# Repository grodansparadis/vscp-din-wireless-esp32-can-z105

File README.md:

# vscp-din-wireless-esp32-z105
ESP32 based CAN4VSCP FD controller in a single module DIN package with BT and wifi interface.

**Note!** This is still a prototype. ....

The bottom board is here: https://github.com/grodansparadis/vscp-din-m1-base-board-z105

## PCB's

---

Part of the [VSCP Project](https://www.vscp.org).

Copyright 2021-2026 © Åke Hedman, (Grodans Paradis AB)[https://www.grodansparadis.com]

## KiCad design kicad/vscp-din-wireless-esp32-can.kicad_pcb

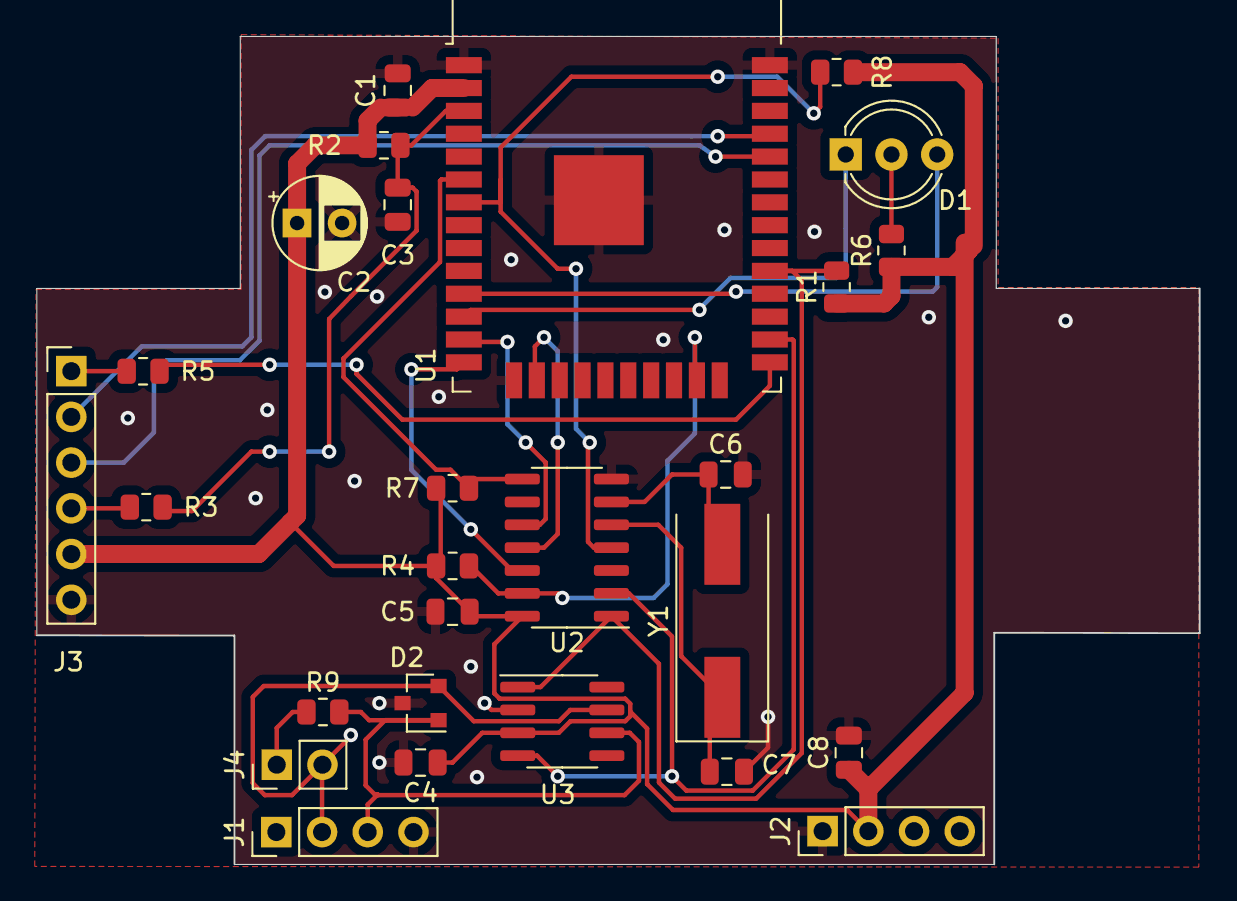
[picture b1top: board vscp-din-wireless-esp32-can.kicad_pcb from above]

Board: 2 copper layers, 64.6 x 46.0 mm, 27 parts (0 on the bottom side), 24 nets.

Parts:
C1, C3, C4, C5, C8: 100nF; C_0805_2012Metric
C2: 10uF; CP_Radial_D5.0mm_P2.50mm
C6, C7: 22pF; C_0805_2012Metric
D1: LED_Dual_CAC; LED_D5.0mm-3
D2: NUP2105L; SOT-23
J1: Conn_Left_I2C; PinHeader_1x04_P2.54mm_Vertical
J2: Conn_Right_Power; PinHeader_1x04_P2.54mm_Vertical
J3: Conn_01x06; PinHeader_1x06_P2.54mm_Vertical
J4: Conn_01x02; PinHeader_1x02_P2.54mm_Vertical
R1, R2, R4, R7, R8: 10K; R_0805_2012Metric
R3, R5, R6: 470; R_0805_2012Metric
R9: 120R; R_0805_2012Metric
U1: ESP32-WROOM-32D; ESP32-WROOM-32
U2: MCP2517FD-xSL; SOIC-14_3.9x8.7mm_P1.27mm
U3: SN65HVD232; SOIC-8_3.9x4.9mm_P1.27mm
Y1: 4MHz; Crystal_SMD_HC49-SD

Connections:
/CS: R4.2, U1.23 (IO15), U2.13 (nCS)
/FLASH: J3.1, R5.2
/MISO: U1.14 (IO12), U2.12 (SDO)
/MOSI: U1.16 (IO13), U2.11 (SDI)
/RESET: J3.4, R3.1
/RXD: J3.3, U1.34 (RXD0/IO3)
/SCK: U1.13 (IO14), U2.10 (SCK)
/TXD: J3.2, U1.35 (TXD0/IO1)
/irq0: R8.1, U1.7 (IO35), U2.4 (~INT)
/irq1: R7.1, U1.6 (IO34), U2.8 (~INT1/GPIO1)
/leda: D1.3 (K2), U1.11 (IO26)
/ledb: D1.1 (K1), U1.12 (IO27)
/reset: C3.1, R2.2, R3.2, U1.3 (EN)
/rxcan: U1.26 (IO4), U2.2 (RXCAN), U3.4 (R)
/txcan: R1.2, U1.29 (IO5), U2.1 (TXCAN), U3.1 (D)
GND: C1.2, C2.2, C3.2, C4.2, C5.2, C6.2, C7.2, C8.2, D2.3 (A), J1.4, J2.1, J3.6, U1.1 (GND), U1.15 (GND), U1.38 (GND), U1.39 (GND), U2.7 (VSS), U3.2 (GND)
unnamed: D1.2 (A), R6.2
unnamed: D2.2 (K), J1.2, J4.2, U3.7 (CANH)
unnamed: D2.1 (K), J1.3, R9.2, U3.6 (CANL)
unnamed: J4.1, R9.1
unnamed: R5.1, U1.25 (IO0)
unnamed: C6.1, U2.6 (OSC1), Y1.2
unnamed: C7.1, U2.5 (OSC2), Y1.1
VCC: C1.1, C2.1, C4.1, C5.1, C8.1, J2.2, J3.5, R1.1, R2.1, R4.1, R6.1, R7.2, R8.2, U1.2 (VDD), U2.14 (VDD), U3.3 (VCC)

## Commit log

2021-05-24 Init import
2021-05-25 First version gerbers
2021-05-25 Added gerbers
2021-05-25 Added notes
2021-08-09 shrinked to fit encapsulationy
    Please enter the commit message for your changes. Lines starting
2021-08-09 Test
2022-02-03 Updatwd copyright
2022-06-15 Fixed some design errors
2022-06-16 Added CAN interace link
2022-06-17 Added BT/serial config info
2022-09-02 Added new libs
2022-09-02 Removed unused images
2022-09-02 Prepared repository name change
2025-06-05 Updated copyright year
2025-09-17 Updated ESP32 module
2026-04-06 Updated to KiCad version 10
2026-04-06 Moved schema to it's own folder
